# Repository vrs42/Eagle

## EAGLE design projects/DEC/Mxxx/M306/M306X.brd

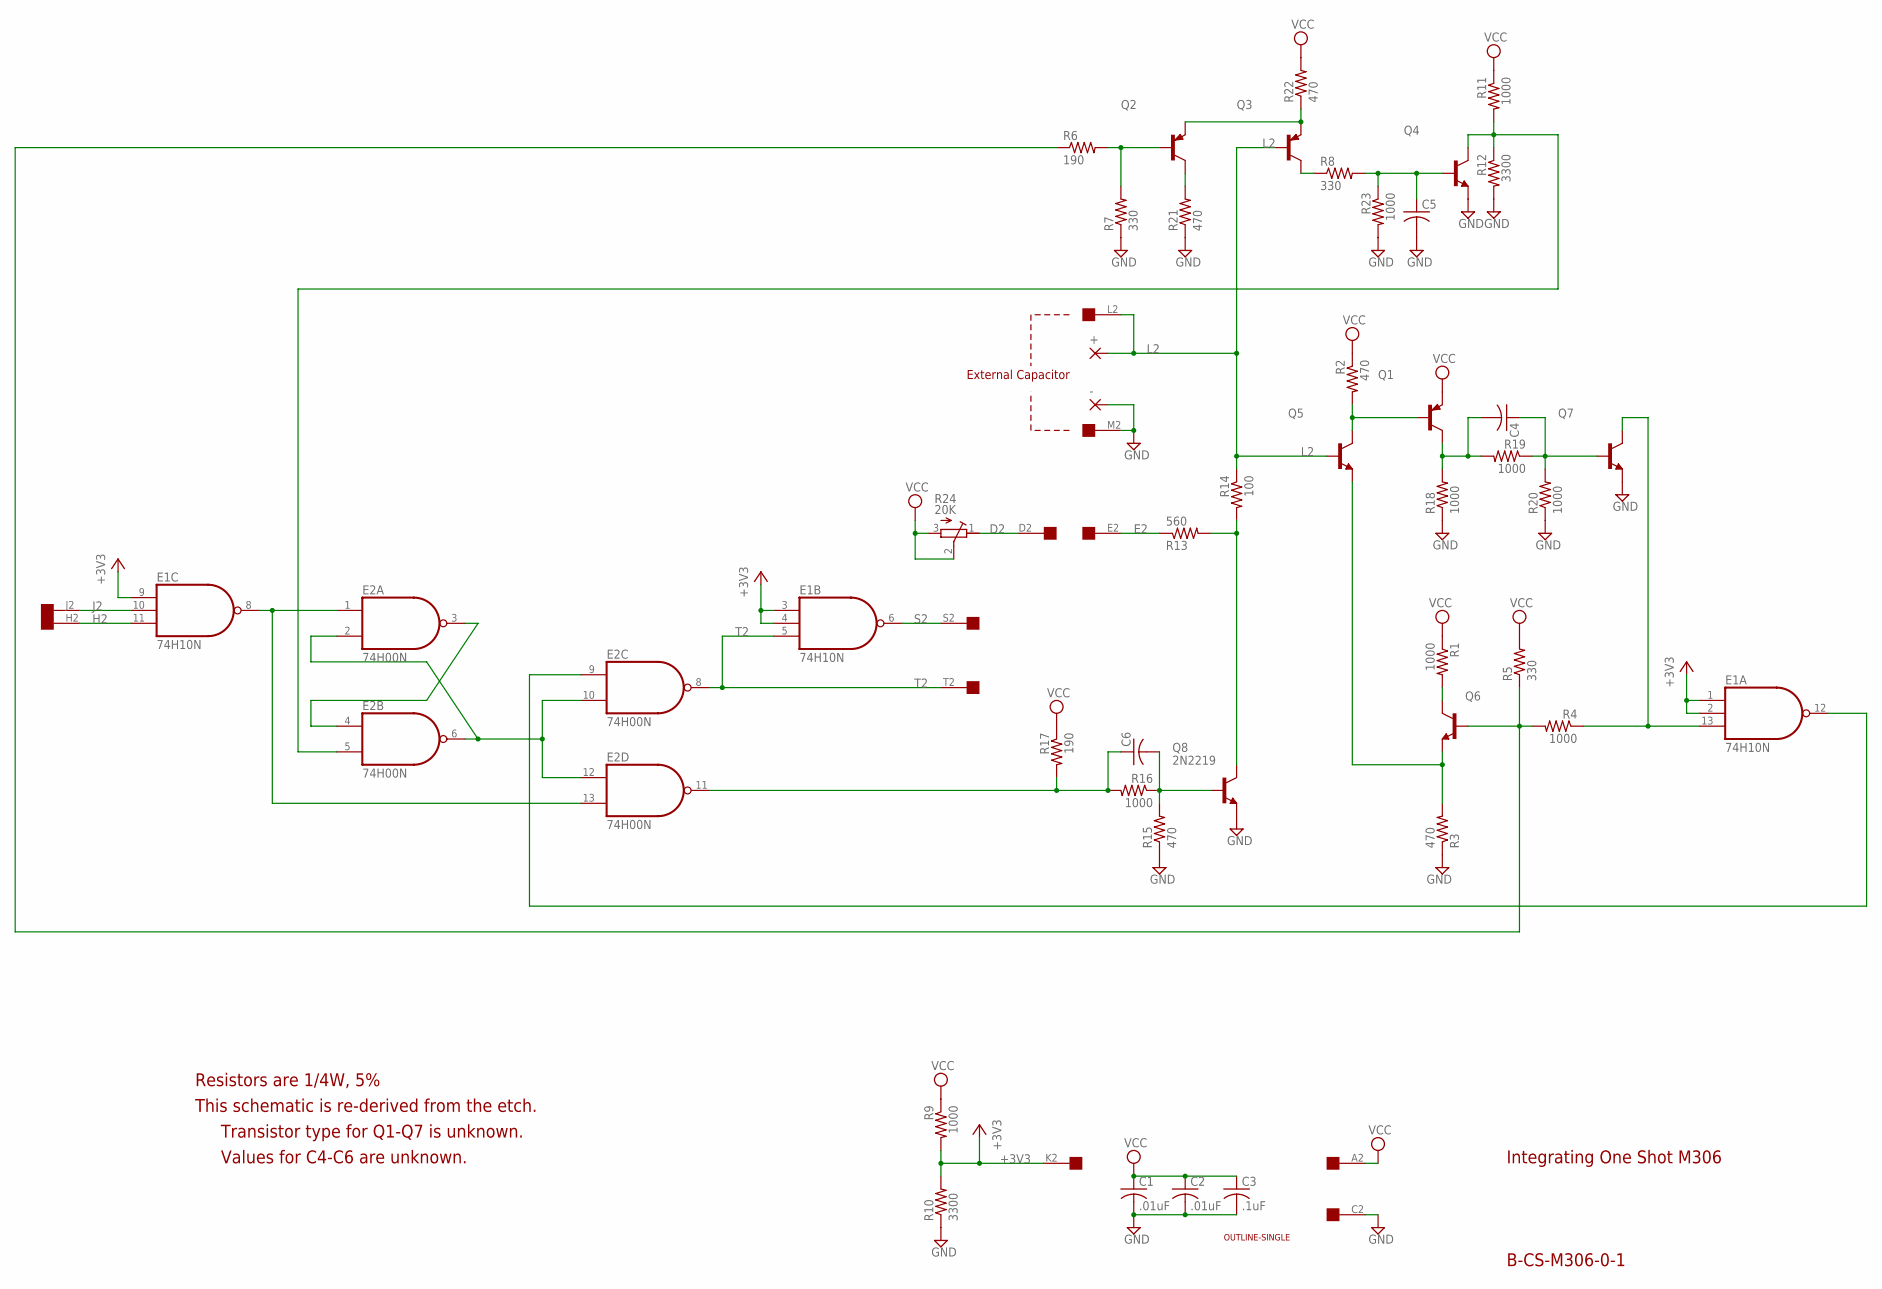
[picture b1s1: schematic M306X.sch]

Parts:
+: 3,17/1,3
-: 3,17/1,3
C1, C2: .01uF; C050-025X075
C3: .1uF; C102-043X133
C4, C5, C6: C-US075-032X103; C075-032X103
E1: 74H10N; DIL14
E2: 74H00N; DIL14
Q1, Q2, Q3: -PNP-TO5; TO5
Q4, Q5, Q6, Q7: 2N3019-NPN-TO39-EBC; TO39
Q8: 2N2219; TO5
R1, R4, R9, R11, R16, R18, R19, R20, R23: 1000; 0207/10
R2, R3, R15, R21, R22: 470; 0207/10
R5, R7, R8: 330; 0207/10
R6, R17: 190; 0207/10
R10, R12: 3300; 0207/10
R13: 560; 0207/10
R14: 100; 0207/10
R24: 20K; 3006Y
U$1: SINGLE; EDGE-CON2
U$2: OUTLINE-SINGLE; SINGLE

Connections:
+3V3: E1.1 (I0), E1.2 (I1), E1.3 (I0), E1.4 (I1), E1.9 (I0), R9.2, R10.2, U$1.K2
D2: R24.1 (A), U$1.D2
E2: R13.1, U$1.E2
GND: -.1, C1.2, C2.2, C3.2, C5.2, E1.7 (GND), E2.7 (GND), Q4.1 (E), Q7.1 (E), Q8.1 (E), R3.1, R7.1, R10.1, R12.2, R15.1, R18.1, R20.1, R21.1, R23.2, U$1.C2, U$1.M2
H2: E1.11 (I2), U$1.H2
J2: E1.10 (I1), U$1.J2
L2: +.1, Q3.2 (B), Q5.2 (B), R14.1, U$1.L2
unnamed: C6.1, E2.11 (O), R16.2, R17.2
unnamed: C6.2, Q8.2 (B), R15.2, R16.1
unnamed: Q8.3 (C), R13.2, R14.2
unnamed: E2.5 (I1), Q4.3 (C), R11.2, R12.1
unnamed: C5.1, Q4.2 (B), R8.2, R23.1
unnamed: Q2.2 (B), R6.2, R7.2
unnamed: Q6.3 (C), R1.2
unnamed: Q1.2 (B), Q5.3 (C), R2.2
unnamed: Q5.1 (E), Q6.1 (E), R3.2
unnamed: Q6.2 (B), R4.2, R5.1, R6.1
unnamed: Q3.3 (C), R8.1
unnamed: E1.13 (I2), Q7.3 (C), R4.1
unnamed: C4.1, Q7.2 (B), R19.1, R20.2
unnamed: E1.8 (O), E2.1 (I0), E2.13 (I1)
unnamed: E1.12 (O), E2.9 (I0)
unnamed: E2.2 (I1), E2.6 (O), E2.10 (I1), E2.12 (I0)
unnamed: E2.3 (O), E2.4 (I0)
unnamed: C4.2, Q1.3 (C), R18.2, R19.2
unnamed: Q2.1 (E), Q3.1 (E), R22.1
unnamed: Q2.3 (C), R21.2
S2: E1.6 (O), U$1.S2
T2: E1.5 (I2), E2.8 (O), U$1.T2
VCC: C1.1, C2.1, C3.1, E1.14 (VCC), E2.14 (VCC), Q1.1 (E), R1.1, R2.1, R5.2, R9.1, R11.1, R17.1, R22.2, R24.2 (S), R24.3 (E), U$1.A2

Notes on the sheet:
Integrating One Shot M306
B-CS-M306-0-1
Resistors are 1/4W, 5%
This schematic is re-derived from the etch.
Transistor type for Q1-Q7 is unknown.
Values for C4-C6 are unknown.
External Capacitor

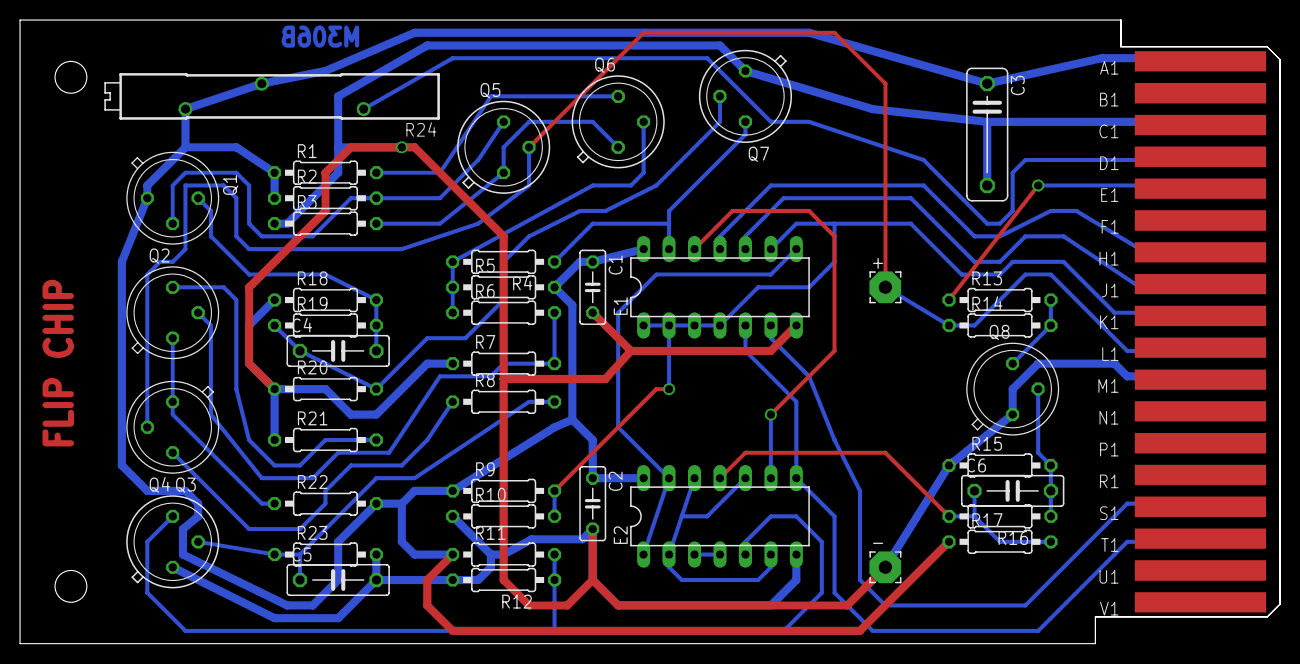
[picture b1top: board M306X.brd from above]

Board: 2 copper layers, 125.7 x 62.2 mm, 45 parts (0 on the bottom side), 30 nets.

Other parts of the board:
U$3: FLIPCHIP

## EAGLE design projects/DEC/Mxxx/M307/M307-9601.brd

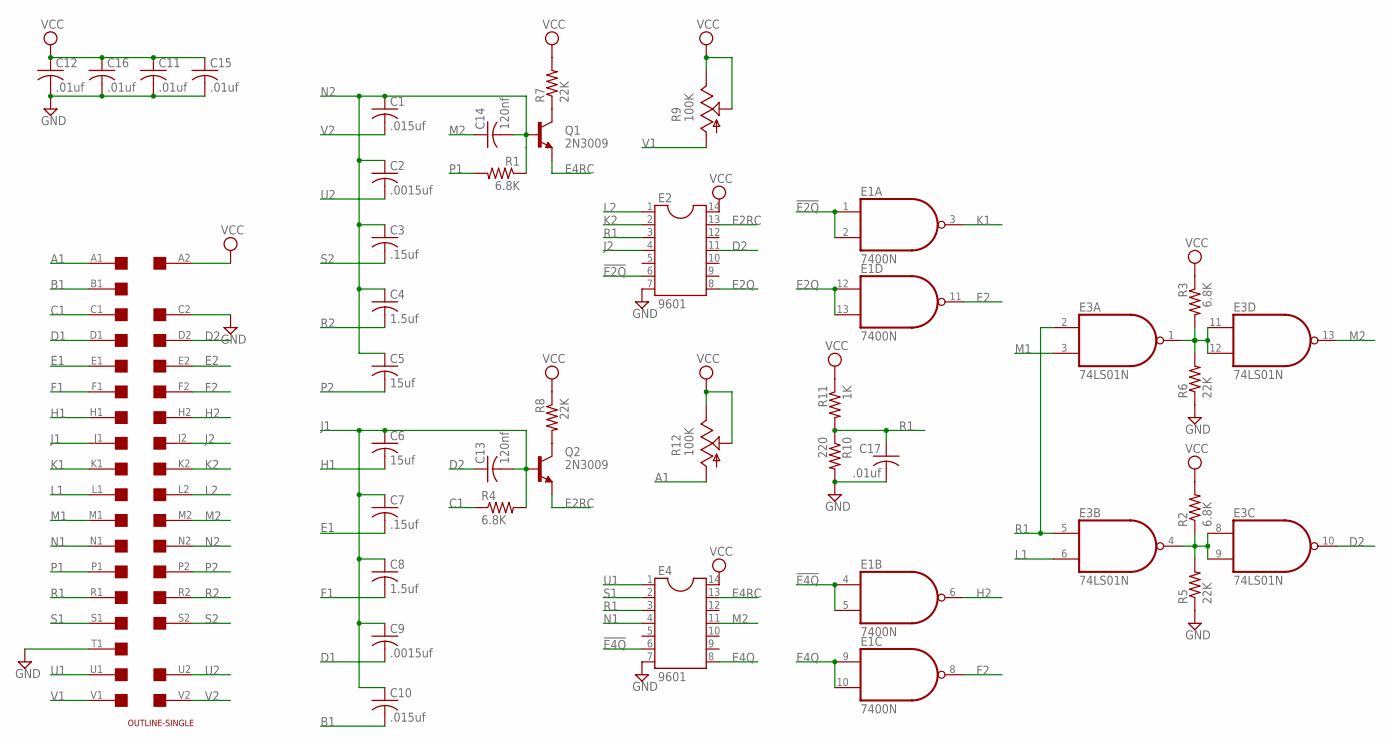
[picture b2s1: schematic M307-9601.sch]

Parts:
C1, C10: .015uf; C150-054X183
C2, C9: .0015uf; C050-025X075
C3, C7: .15uf; C102-043X133
C4, C8: 1.5uf; C150-054X183
C5, C6: 15uf; C150-054X183
C11, C12, C15, C16, C17: .01uf; C050-025X075
C13, C14: 120nf; C075-032X103
E1: 7400N; DIL14
E2, E4: 9601; DIL14
E3: 74LS01N; DIL14
Q1, Q2: 2N3009; TO39
R1, R2, R3, R4: 6.8K; 0207/10
R5, R6, R7, R8: 22K; 0207/10
R9, R12: 100K; PT-SPIN
R10: 220; 0207/10
R11: 1K; 0207/10
U$1: OUTLINE-SINGLE; SINGLE
U$4: SINGLE; EDGE-CON2

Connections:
!E2Q: E1.1 (I0), E1.2 (I1), E2.6
!E4Q: E1.4 (I0), E1.5 (I1), E4.6
A1: R12.A, U$4.A1
B1: C10.2, U$4.B1
C1: R4.1, U$4.C1
D1: C9.2, U$4.D1
D2: C13.1, E2.11, E3.10 (O), U$4.D2
E1: C7.2, U$4.E1
E2: E1.11 (O), U$4.E2
E2Q: E1.12 (I0), E1.13 (I1), E2.8
E2RC: E2.13, Q2.1 (E)
E4Q: E1.9 (I0), E1.10 (I1), E4.8
E4RC: E4.13, Q1.1 (E)
F1: C8.2, U$4.F1
F2: E1.8 (O), U$4.F2
GND: C11.2, C12.2, C15.2, C16.2, C17.2, E1.7 (GND), E2.7, E3.7 (GND), E4.7, R5.1, R6.1, R10.2, U$4.C2, U$4.T1
H1: C6.2, U$4.H1
H2: E1.6 (O), U$4.H2
J1: C6.1, C7.1, C8.1, C9.1, C10.1, C13.2, Q2.2 (B), R4.2, U$4.J1
J2: E2.4, U$4.J2
K1: E1.3 (O), U$4.K1
K2: E2.2, U$4.K2
L1: E3.6 (I1), U$4.L1
L2: E2.1, U$4.L2
M1: E3.3 (I1), U$4.M1
M2: C14.1, E3.13 (O), E4.11, U$4.M2
N1: E4.4, U$4.N1
N2: C1.1, C2.1, C3.1, C4.1, C5.1, C14.2, Q1.2 (B), R1.1, U$4.N2
unnamed: Q1.3 (C), R7.1
unnamed: E3.4 (O), E3.8 (I0), E3.9 (I1), R2.1, R5.2
unnamed: Q2.3 (C), R8.2
unnamed: E3.1 (O), E3.11 (I0), E3.12 (I1), R3.2, R6.2
P1: R1.2, U$4.P1
P2: C5.2, U$4.P2
R1: C17.1, E2.3, E3.2 (I0), E3.5 (I0), E4.3, R10.1, R11.2, U$4.R1
R2: C4.2, U$4.R2
S1: E4.2, U$4.S1
S2: C3.2, U$4.S2
U1: E4.1, U$4.U1
U2: C2.2, U$4.U2
V1: R9.A, U$4.V1
V2: C1.2, U$4.V2
VCC: C11.1, C12.1, C15.1, C16.1, E1.14 (VCC), E2.14, E3.14 (VCC), E4.14, R2.2, R3.1, R7.2, R8.1, R9.E, R9.S, R11.1, R12.E, R12.S, U$4.A2

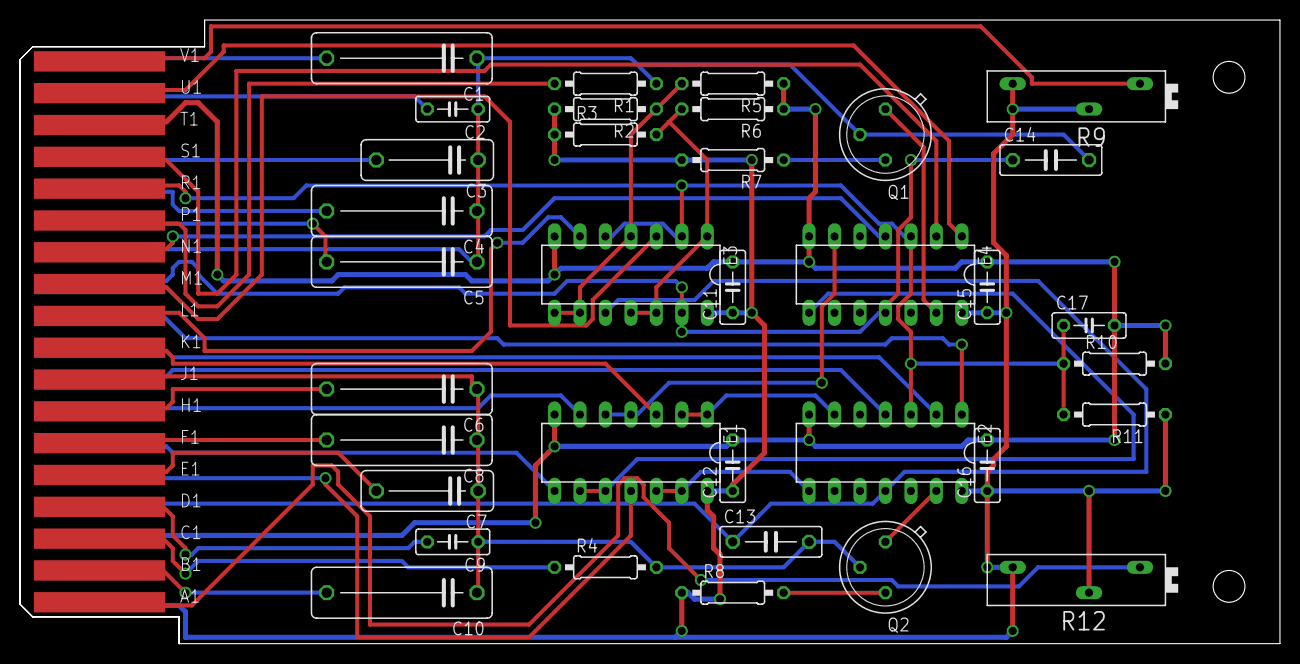
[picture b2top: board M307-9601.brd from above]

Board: 2 copper layers, 125.7 x 62.2 mm, 37 parts (0 on the bottom side), 43 nets.

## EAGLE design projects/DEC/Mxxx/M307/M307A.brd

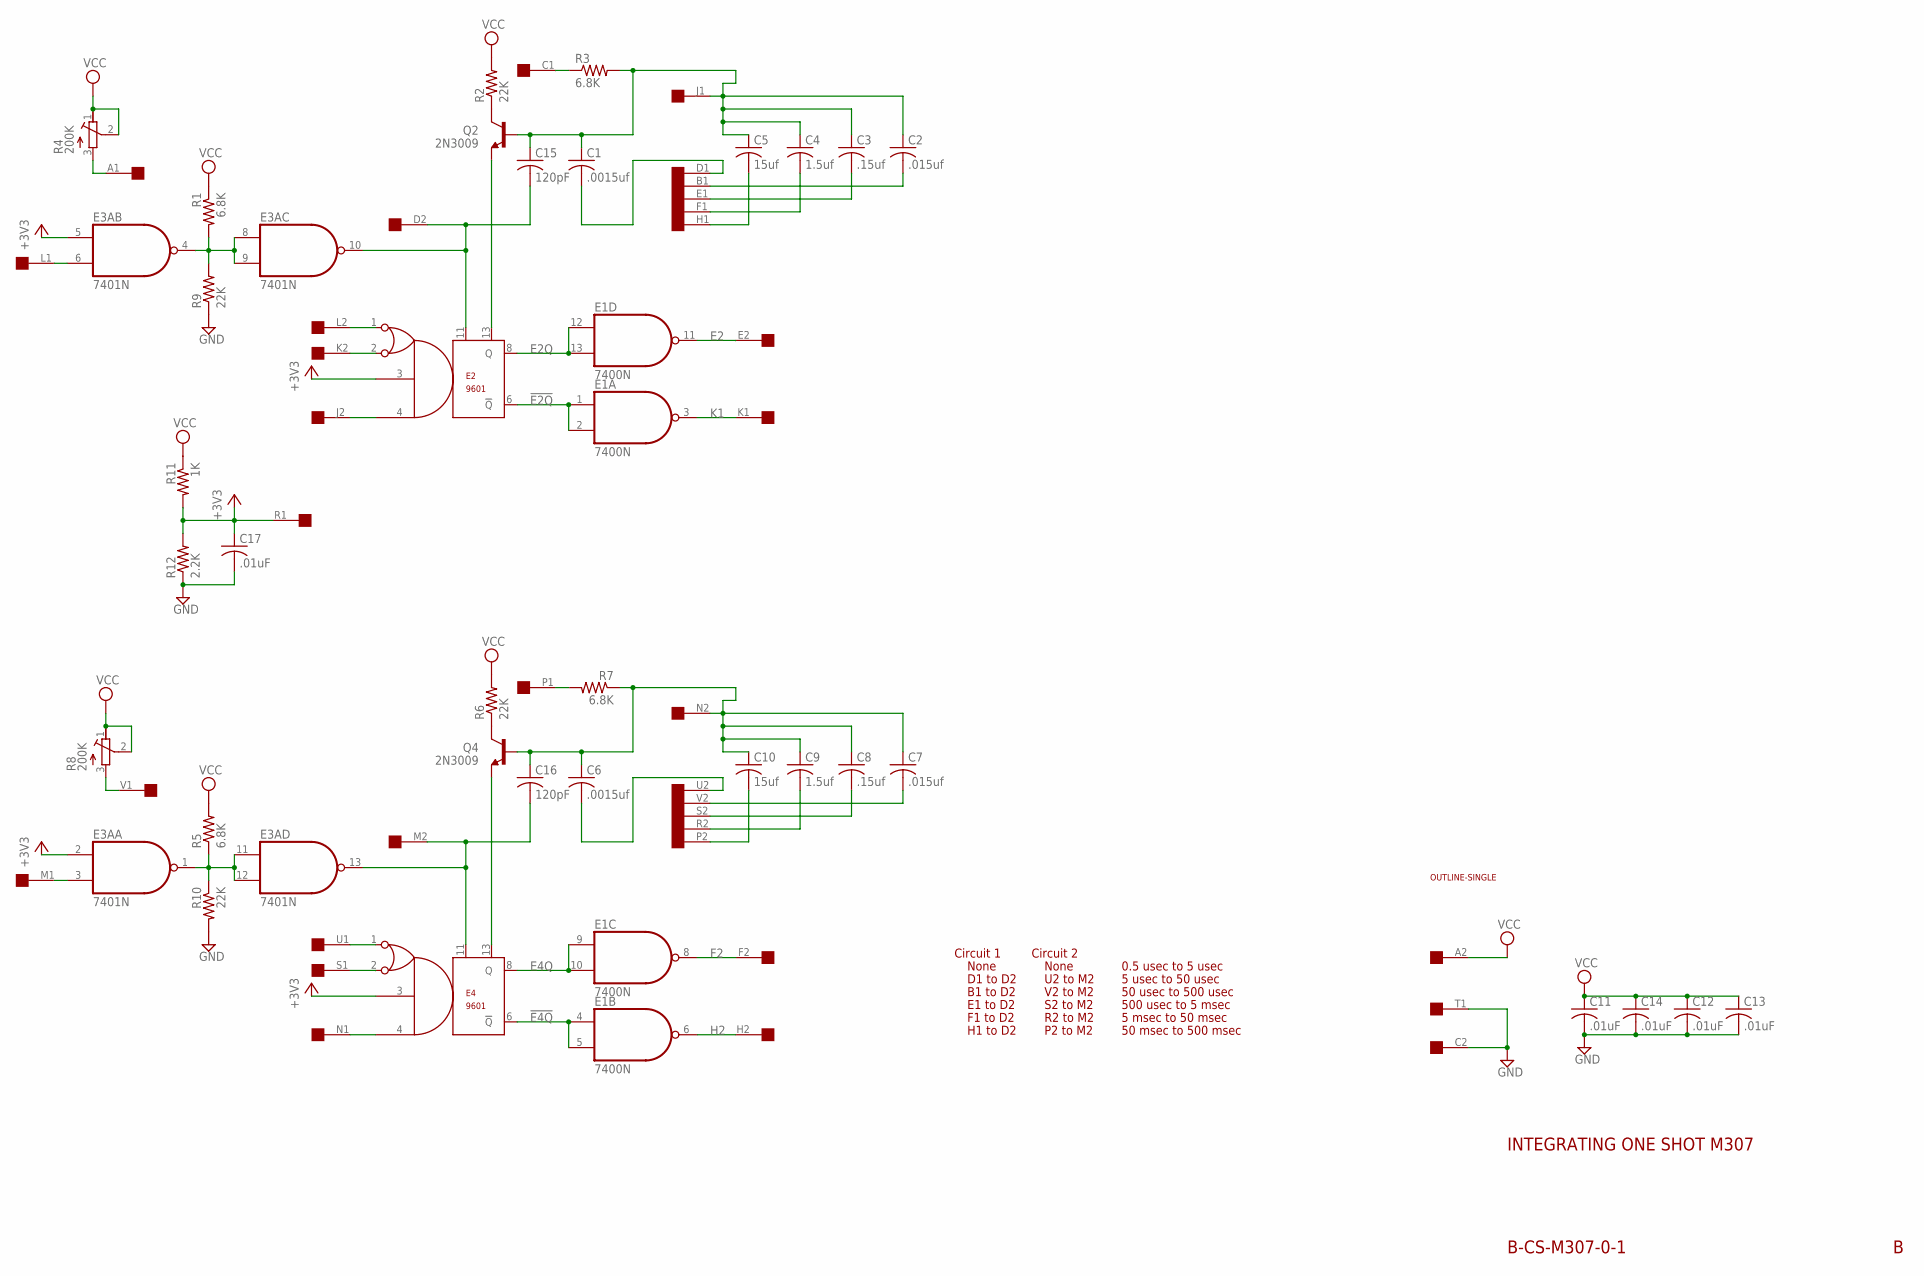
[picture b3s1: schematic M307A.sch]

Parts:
C1, C6: .0015uf; C050-025X075
C2, C7: .015uf; C150-054X183
C3, C8: .15uf; C102-054X133
C4, C9: 1.5uf; C150-054X183
C5, C10: 15uf; C150-054X183
C11, C12, C13, C14, C17: .01uF; C050-025X075
C15, C16: 120pF; C050-025X075
E1: 7400N; DIL14
E2, E4: 9601; DIL14
E3A: 7401N; DIL14
Q2, Q4: 2N3009; TO39
R1, R3, R5, R7: 6.8K; 0207/10
R2, R6, R9, R10: 22K; 0207/10
R4, R8: 200K; 3006Y
R11: 1K; 0207/10
R12: 2.2K; 0207/10
U$1: OUTLINE-SINGLE; SINGLE
U$4: SINGLE; EDGE-CON2

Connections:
!E2Q: E1.1 (I0), E1.2 (I1), E2.6 (!Q)
!E4Q: E1.4 (I0), E1.5 (I1), E4.6 (!Q)
+3V3: C17.1, E2.3, E3A.2 (I0), E3A.5 (I0), E4.3, R11.2, R12.2, U$4.R1
A1: R8.3 (E), U$4.V1
C1: R3.1, U$4.C1
E2: E1.11 (O), U$4.E2
E2Q: E1.12 (I0), E1.13 (I1), E2.8 (Q)
E4Q: E1.9 (I0), E1.10 (I1), E4.8 (Q)
F2: E1.8 (O), U$4.F2
GND: C11.2, C12.2, C13.2, C14.2, C17.2, E1.7 (GND), E2.7 (GND), E3A.7 (GND), E4.7 (GND), R9.1, R10.2, R12.1, U$4.C2, U$4.T1
H2: E1.6 (O), U$4.H2
J1: E3A.1 (O), E3A.11 (I0), E3A.12 (I1), R5.1, R10.1
J2: E2.4, U$4.J2
K1: E1.3 (O), U$4.K1
K2: E2.2, U$4.K2
L1: E3A.6 (I1), U$4.L1
L2: E2.1, U$4.L2
M1: E3A.3 (I1), U$4.M1
N1: E4.4, U$4.N1
unnamed: E4.13, Q4.1 (E)
unnamed: E3A.4 (O), E3A.8 (I0), E3A.9 (I1), R1.2, R9.2
unnamed: C1.1, C2.1, C3.1, C4.1, C5.1, C15.1, Q2.2 (B), R3.2, U$4.J1
unnamed: C6.2, U$4.U2
unnamed: C15.2, E2.11, E3A.10 (O), U$4.D2
unnamed: C16.2, E3A.13 (O), E4.11, U$4.M2
unnamed: C2.2, U$4.B1
unnamed: C3.2, U$4.E1
unnamed: C4.2, U$4.F1
unnamed: C5.2, U$4.H1
unnamed: C6.1, C7.1, C8.1, C9.1, C10.1, C16.1, Q4.2 (B), R7.1, U$4.N2
unnamed: C10.2, U$4.P2
unnamed: C9.2, U$4.R2
unnamed: C8.2, U$4.S2
unnamed: C7.2, U$4.V2
unnamed: C1.2, U$4.D1
unnamed: E2.13, Q2.1 (E)
unnamed: Q2.3 (C), R2.1
unnamed: Q4.3 (C), R6.1
P1: R7.2, U$4.P1
S1: E4.2, U$4.S1
U1: E4.1, U$4.U1
V1: R4.3 (E), U$4.A1
VCC: C11.1, C12.1, C13.1, C14.1, E1.14 (VCC), E2.14 (VCC), E3A.14 (VCC), E4.14 (VCC), R1.1, R2.2, R4.1 (A), R4.2 (S), R5.2, R6.2, R8.1 (A), R8.2 (S), R11.1, U$4.A2

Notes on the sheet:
B-CS-M307-0-1
INTEGRATING ONE SHOT M307
U2 to M2
V2 to M2
S2 to M2
R2 to M2
P2 to M2
5 usec to 50 usec
50 usec to 500 usec
500 usec to 5 msec
5 msec to 50 msec
50 msec to 500 msec
D1 to D2
B1 to D2
E1 to D2
F1 to D2
H1 to D2
None
0.5 usec to 5 usec
Circuit 1
Circuit 2

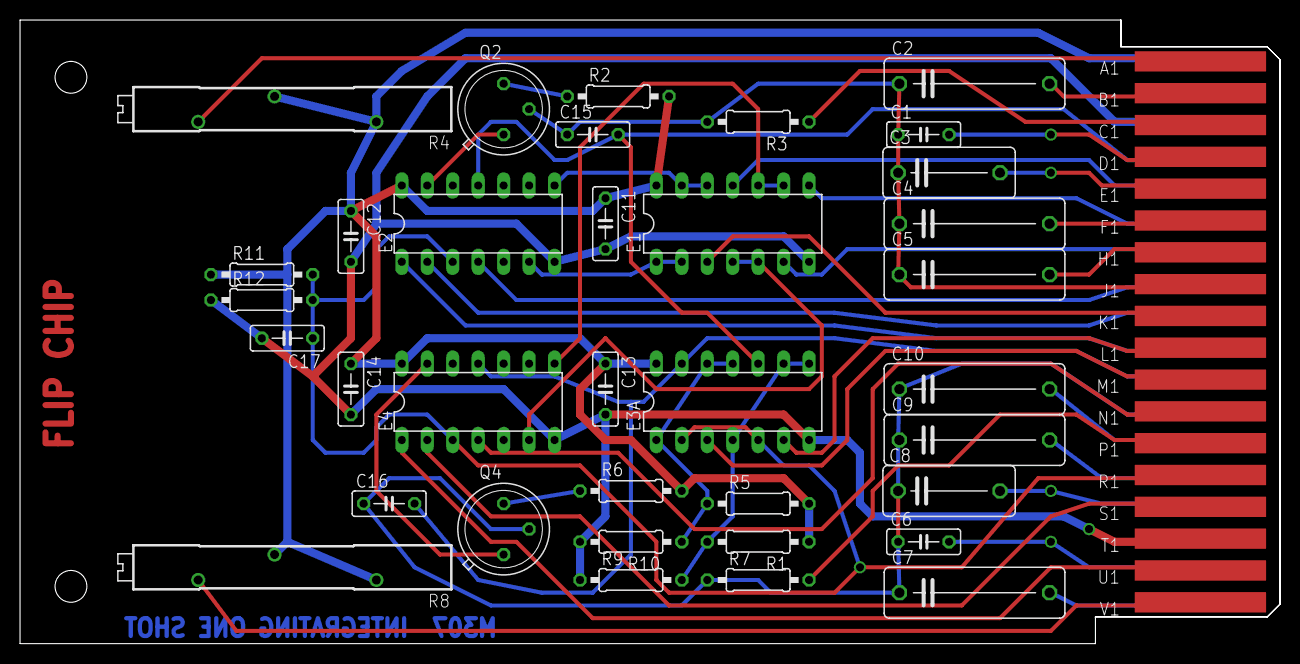
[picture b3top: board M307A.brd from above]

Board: 2 copper layers, 125.7 x 62.2 mm, 38 parts (0 on the bottom side), 43 nets.

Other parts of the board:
U$3: FLIPCHIP

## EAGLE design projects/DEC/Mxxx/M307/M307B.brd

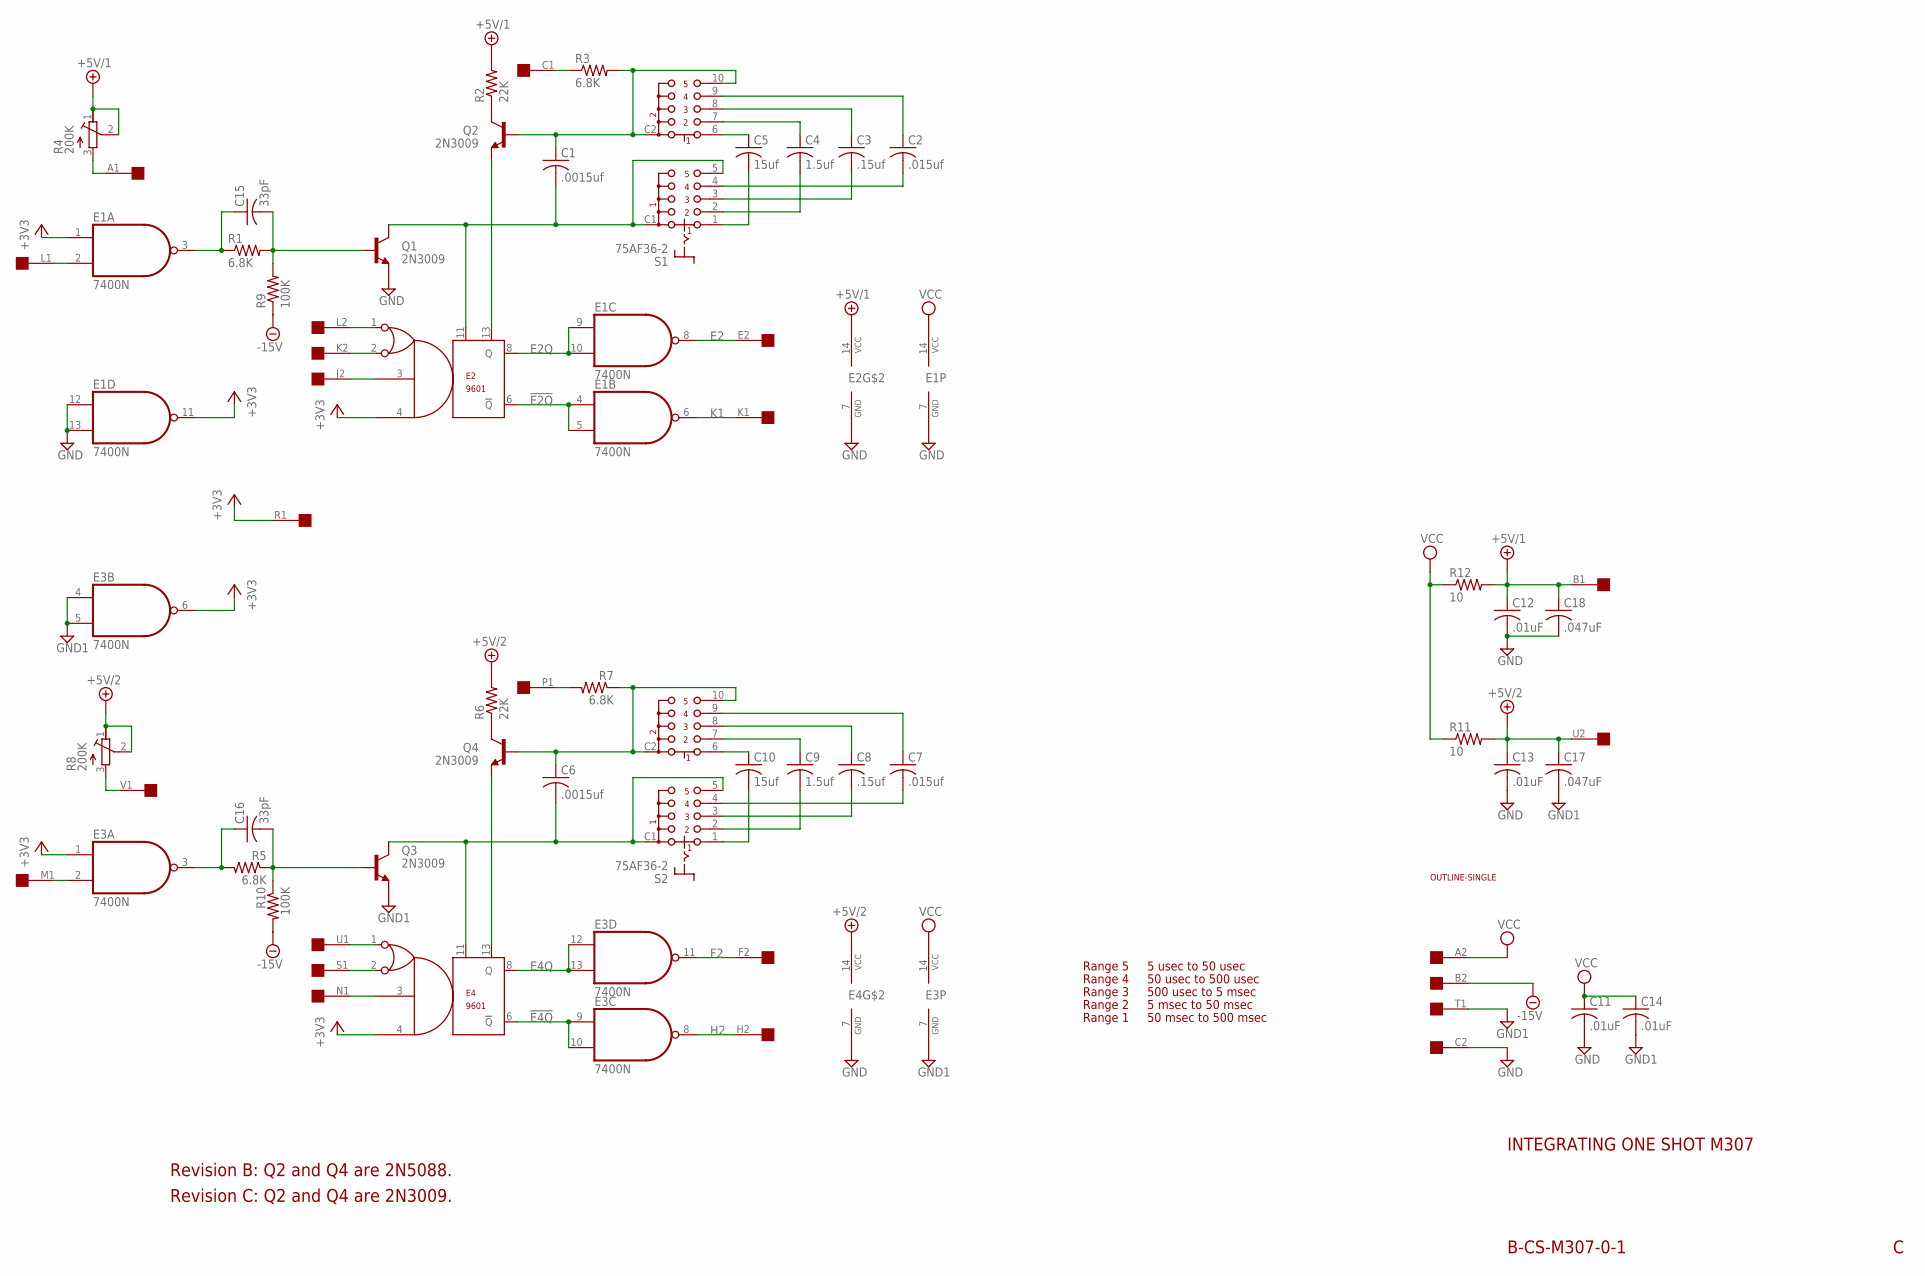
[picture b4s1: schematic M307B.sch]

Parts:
C1, C6: .0015uf; C050-025X075
C2, C7: .015uf; C150-054X183
C3, C8: .15uf; C150-054X183
C4, C9: 1.5uf; C150-054X183
C5, C10: 15uf; C150-054X183
C11, C12, C13, C14: .01uF; C050-025X075
C15, C16: 33pF; C050-025X075
C17, C18: .047uF; C050-025X075
E1, E3: 7400N; DIL14
E2, E4: 9601; DIL14
Q1, Q2, Q3, Q4: 2N3009; TO39
R1, R3, R5, R7: 6.8K; 0207/10
R2, R6: 22K; 0207/10
R4, R8: 200K; 3006Y
R9, R10: 100K; 0207/10
R11, R12: 10; 0207/10
S1, S2: 75AF36-2
U$1: OUTLINE-SINGLE; SINGLE
U$4: SINGLE; EDGE-CON2

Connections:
!E2Q: E1.4 (I0), E1.5 (I1), E2.6 (!Q)
!E4Q: E3.9 (I0), E3.10 (I1), E4.6 (!Q)
+3V3: E1.1 (I0), E1.11 (O), E2.4, E3.1 (I0), E3.6 (O), E4.4, U$4.R1
+5V/1: C12.1, C18.1, E2.14 (VCC), R2.2, R4.1 (A), R4.2 (S), R12.2, U$4.B1
+5V/2: C13.1, C17.1, E4.14 (VCC), R6.2, R8.1 (A), R8.2 (S), R11.2, U$4.U2
-15V: R9.1, R10.2, U$4.B2
A1: R8.3 (E), U$4.V1
C1: R3.1, U$4.C1
E2: E1.8 (O), U$4.E2
E2Q: E1.9 (I0), E1.10 (I1), E2.8 (Q)
E4Q: E3.12 (I0), E3.13 (I1), E4.8 (Q)
F2: E3.11 (O), U$4.F2
GND: C11.2, C12.2, C13.2, C18.2, E1.7 (GND), E1.12 (I0), E1.13 (I1), E2.7 (GND), E4.7 (GND), Q1.1 (E), U$4.C2
GND1: C14.2, C17.2, E3.4 (I0), E3.5 (I1), E3.7 (GND), Q3.1 (E), U$4.T1
H2: E3.8 (O), U$4.H2
J1: C16.2, Q3.2 (B), R5.1, R10.1
J2: E2.3, U$4.J2
K1: E1.6 (O), U$4.K1
K2: E2.2, U$4.K2
L1: E1.2 (I1), U$4.L1
L2: E2.1, U$4.L2
M1: E3.2 (I1), U$4.M1
N1: E4.3, U$4.N1
unnamed: E4.13, Q4.1 (E)
unnamed: C15.1, E1.3 (O), R1.1
unnamed: C16.1, E3.3 (O), R5.2
unnamed: C5.1, S1.6 (12)
unnamed: C6.2, E4.11, Q3.3 (C), S2.5 (51), S2.C1
unnamed: C4.1, S1.7 (22)
unnamed: C3.1, S1.8 (32)
unnamed: C2.1, S1.9 (42)
unnamed: C2.2, S1.4 (41)
unnamed: C3.2, S1.3 (31)
unnamed: C4.2, S1.2 (21)
unnamed: C5.2, S1.1 (11)
unnamed: C10.1, S2.6 (12)
unnamed: C9.1, S2.7 (22)
unnamed: C8.1, S2.8 (32)
unnamed: C7.1, S2.9 (42)
unnamed: C10.2, S2.1 (11)
unnamed: C9.2, S2.2 (21)
unnamed: C8.2, S2.3 (31)
unnamed: C7.2, S2.4 (41)
unnamed: C1.1, Q2.2 (B), R3.2, S1.10 (52), S1.C2
unnamed: C1.2, E2.11, Q1.3 (C), S1.5 (51), S1.C1
unnamed: C6.1, Q4.2 (B), R7.1, S2.10 (52), S2.C2
unnamed: E2.13, Q2.1 (E)
unnamed: Q2.3 (C), R2.1
unnamed: Q4.3 (C), R6.1
unnamed: C15.2, Q1.2 (B), R1.2, R9.2
P1: R7.2, U$4.P1
S1: E4.2, U$4.S1
U1: E4.1, U$4.U1
V1: R4.3 (E), U$4.A1
VCC: C11.1, C14.1, E1.14 (VCC), E3.14 (VCC), R11.1, R12.1, U$4.A2

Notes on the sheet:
B-CS-M307-0-1
INTEGRATING ONE SHOT M307
Revision C: Q2 and Q4 are 2N3009.
Revision B: Q2 and Q4 are 2N5088.
Range 5
Range 4
Range 3
Range 2
Range 1
5 usec to 50 usec
50 usec to 500 usec
500 usec to 5 msec
5 msec to 50 msec
50 msec to 500 msec

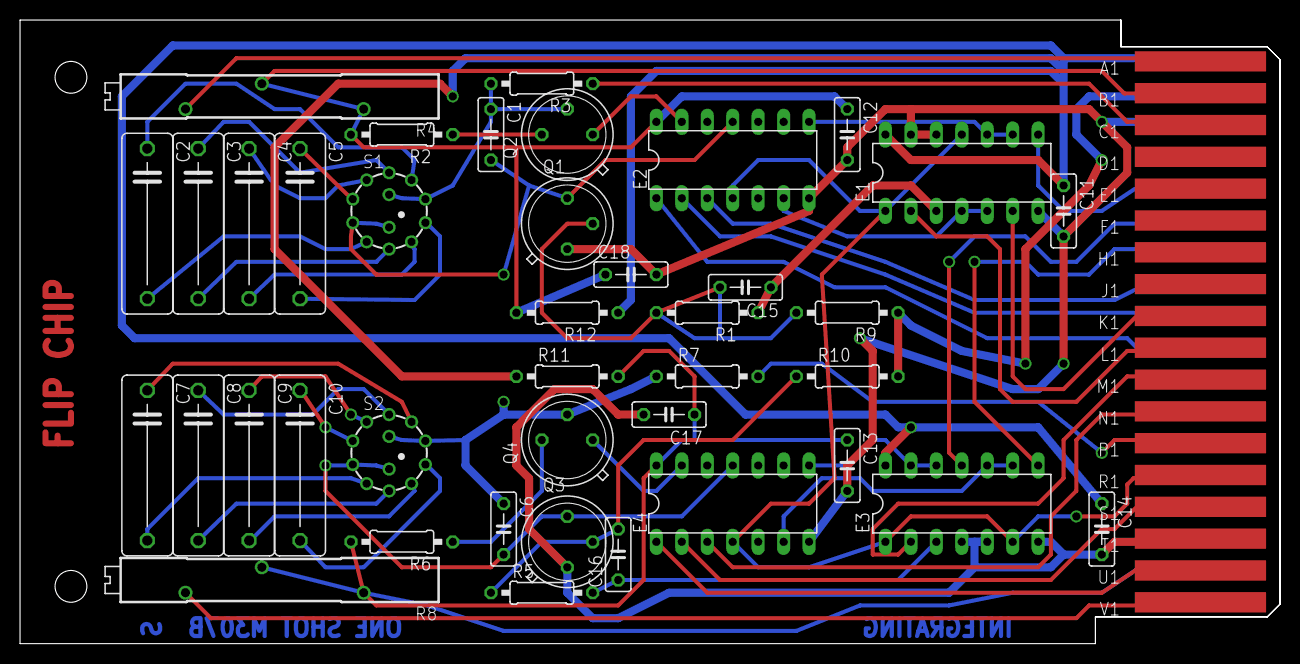
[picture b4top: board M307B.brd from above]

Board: 2 copper layers, 125.7 x 62.2 mm, 43 parts (0 on the bottom side), 55 nets.

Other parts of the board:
U$3: FLIPCHIP
